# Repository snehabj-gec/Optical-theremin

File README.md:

# Optical-theremin
Design and development of an analog optical theremin using NE555,LM358,LM386 and light dependent resistors(LDRs).

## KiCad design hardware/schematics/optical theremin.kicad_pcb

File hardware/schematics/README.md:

Circuit Schematic

Optical Theremin

This folder contains the circuit schematic of the Optical Theremin project, a fully analog musical instrument that generates sound by detecting changes in light intensity.

Circuit Overview

The circuit consists of the following main stages:

1. NE555 Timer: Configured in astable mode to generate a square-wave signal. The oscillation frequency changes according to the resistance of the pitch-control LDR.
2. LM358 Op-Amp: Used for signal buffering and conditioning.
3. Volume Control: A second LDR controls the output volume based on the amount of light falling on it.
4. LM386 Audio Amplifier: Amplifies the generated audio signal to drive the speaker.
5. Power Supply: The circuit operates using a 9V supply.

Working Principle

The Optical Theremin uses two Light Dependent Resistors (LDRs) to provide contactless control over sound.

- The pitch-control LDR changes the oscillation frequency of the NE555 timer.
- The volume-control LDR controls the amplitude of the audio output.
- The generated signal is processed and amplified before being delivered to the speaker.

Moving your hands over the LDRs changes the amount of light reaching them, thereby changing the sound.

Components Used

- NE555 Timer IC
- LM358 Operational Amplifier
- LM386 Audio Amplifier
- 2 × LDRs
- Resistors
- Capacitors
- Speaker
- 9V Battery / Power Supply

Schematic

The circuit schematic is provided in this folder.

Notes

This project was designed as a simple, low-cost, fully analog implementation of an Optical Theremin for educational purposes.

Total project expenditure: ₹457

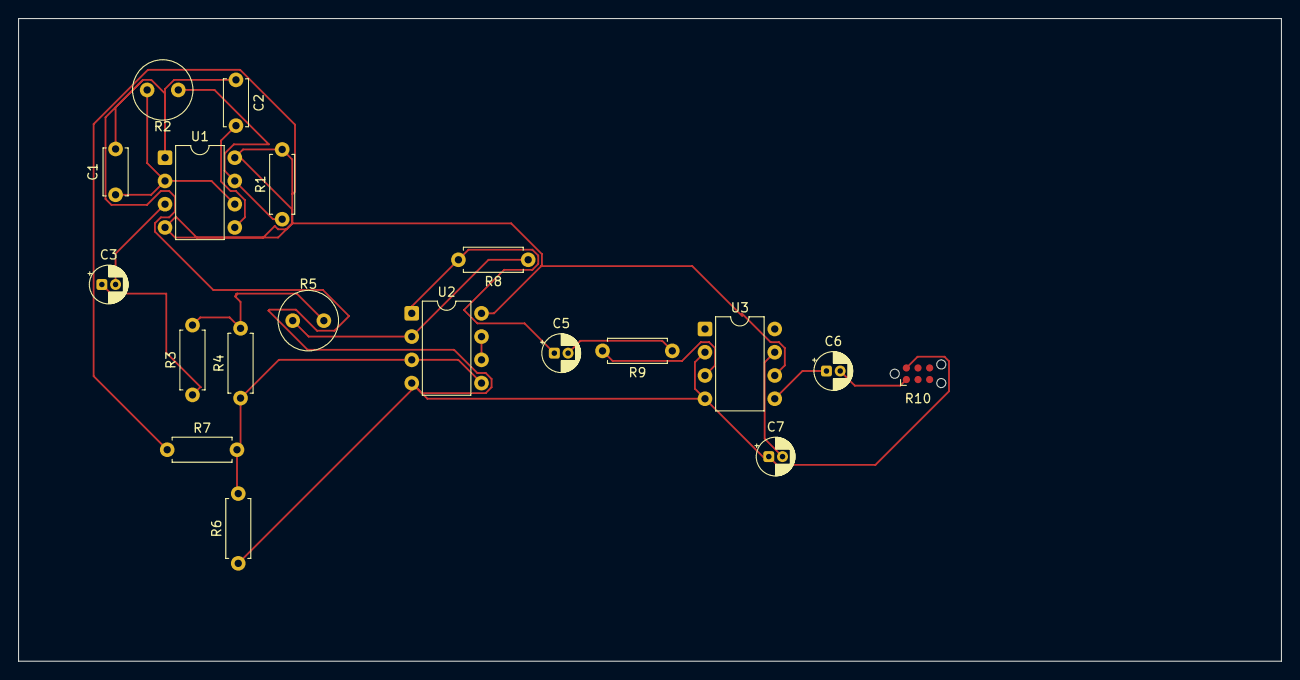
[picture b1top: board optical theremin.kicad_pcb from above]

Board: 2 copper layers, 137.9 x 70.2 mm, 19 parts (0 on the bottom side), 17 nets.

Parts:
C1: 39n; C_Disc_D5.0mm_W2.5mm_P5.00mm
C2: 0.01u; C_Disc_D5.0mm_W2.5mm_P5.00mm
C3: 47u; CP_Radial_D4.0mm_P1.50mm
C5, C7: 10u; CP_Radial_D4.0mm_P1.50mm
C6: 1000u; CP_Radial_D4.0mm_P1.50mm
R1: 1k; R_Axial_DIN0207_L6.3mm_D2.5mm_P7.62mm_Horizontal
R2, R5: A1050; R_LDR_D6.4mm_P3.4mm_Vertical
R3: 22k; R_Axial_DIN0207_L6.3mm_D2.5mm_P7.62mm_Horizontal
R4: 470; R_Axial_DIN0207_L6.3mm_D2.5mm_P7.62mm_Horizontal
R6, R7, R9: 10k; R_Axial_DIN0207_L6.3mm_D2.5mm_P7.62mm_Horizontal
R8: 6.8k; R_Axial_DIN0207_L6.3mm_D2.5mm_P7.62mm_Horizontal
R10: 8; Tag-Connect_TC2030-IDC-NL_2x03_P1.27mm_Vertical
U1: LM555xM; DIP-8_W7.62mm
U2: LM358; DIP-8_W7.62mm
U3: LM386; DIP-8_W7.62mm

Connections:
+9V: R1.2, R7.1, U1.4 (~RST), U1.8 (VCC), U2.8 (V+), U3.6 (V+)
GND: C1.2, C2.1, C7.1, R6.1, R10.2, U1.1 (GND), U2.4 (V-), U3.2 (-), U3.4 (GND)
unnamed: C3.1, R3.1
unnamed: C5.1, R8.2, U2.1
unnamed: C5.2, R9.1
unnamed: C6.1, U3.5
unnamed: C6.2, R10.1
unnamed: R3.2, R4.2, R5.2
unnamed: C2.2, U1.5 (CONT)
unnamed: R1.1, R2.1, U1.7 (DISCH)
unnamed: C3.2, U1.3 (OUT)
unnamed: C1.1, R2.2, U1.2 (TRIG), U1.6 (THRES)
unnamed: R4.1, R6.2, R7.2, U2.3 (+), U2.5 (+)
unnamed: R5.1, R8.1, U2.2 (-)
unnamed: U2.6 (-), U2.7
unnamed: R9.2, U3.3 (+)
unnamed: C7.2, U3.7 (BYPASS)
